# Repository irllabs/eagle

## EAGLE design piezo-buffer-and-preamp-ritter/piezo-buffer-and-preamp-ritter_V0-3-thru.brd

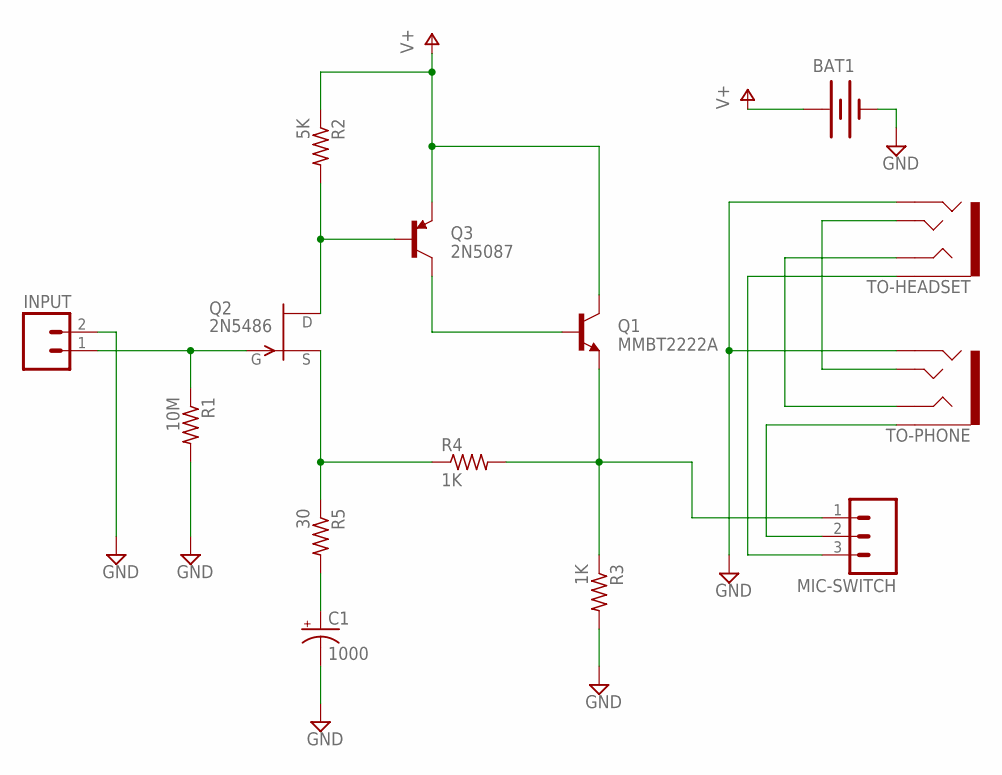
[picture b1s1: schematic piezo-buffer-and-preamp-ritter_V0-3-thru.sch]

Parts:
BAT1: BATTERYAAA-KIT; BATTERY-AAA-KIT
C1: 1000; CPOL-RADIAL-1000UF-25V
INPUT: M02LOCK; 1X02_LOCK
MIC-SWITCH: M03LOCK; 1X03_LOCK
Q1: MMBT2222A; TO-92
Q2: 2N5486; TO92-
Q3: 2N5087; TO-92
R1: 10M; V526-0
R2: 5K; V526-0
R3, R4: 1K; V526-0
R5: 30; V526-0
TO-HEADSET: AUDIO-JACK3; AUDIO-JACK-TRRS-SMD
TO-PHONE: AUDIO-JACK3; AUDIO-JACK-TRRS-SMD

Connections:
GND: BAT1.GND@1 (-), C1.-, INPUT.2, R1.2, R3.2, TO-HEADSET.RING2, TO-PHONE.RING2
unnamed: INPUT.1, Q2.1 (G), R1.1
unnamed: Q2.3 (D), Q3.2 (B), R2.2
unnamed: Q2.2 (S), R4.1, R5.1
unnamed: Q1.2 (B), Q3.3 (C)
unnamed: C1.+, R5.2
unnamed: MIC-SWITCH.3, TO-HEADSET.EARTH
unnamed: TO-HEADSET.TIP, TO-PHONE.TIP
unnamed: TO-HEADSET.RING1, TO-PHONE.RING1
TO-PHONE: MIC-SWITCH.2, TO-PHONE.EARTH
V+: BAT1.PWR@1 (+), Q1.3 (C), Q3.1 (E), R2.1
`DEL: MIC-SWITCH.1, Q1.1 (E), R3.1, R4.2

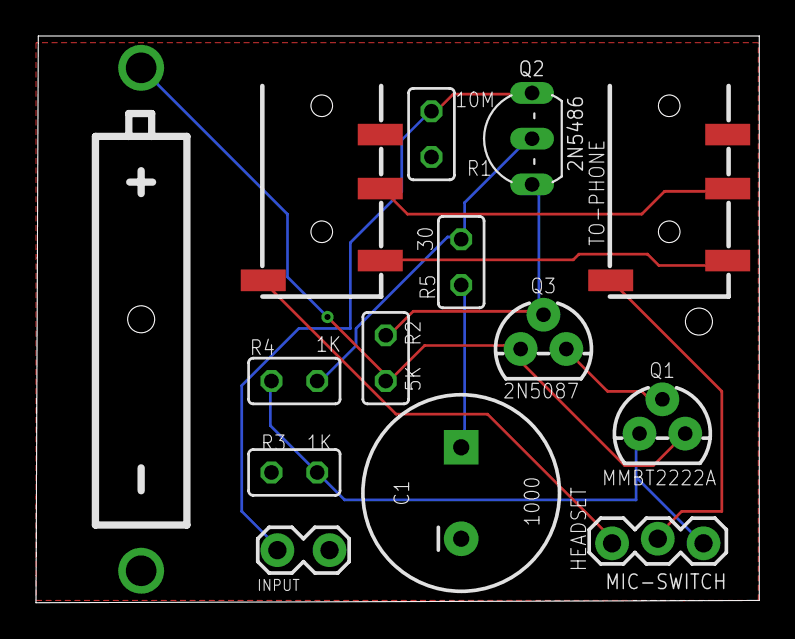
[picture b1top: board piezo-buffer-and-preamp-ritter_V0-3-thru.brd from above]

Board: 2 copper layers, 40.2 x 31.5 mm, 14 parts (0 on the bottom side), 12 nets.

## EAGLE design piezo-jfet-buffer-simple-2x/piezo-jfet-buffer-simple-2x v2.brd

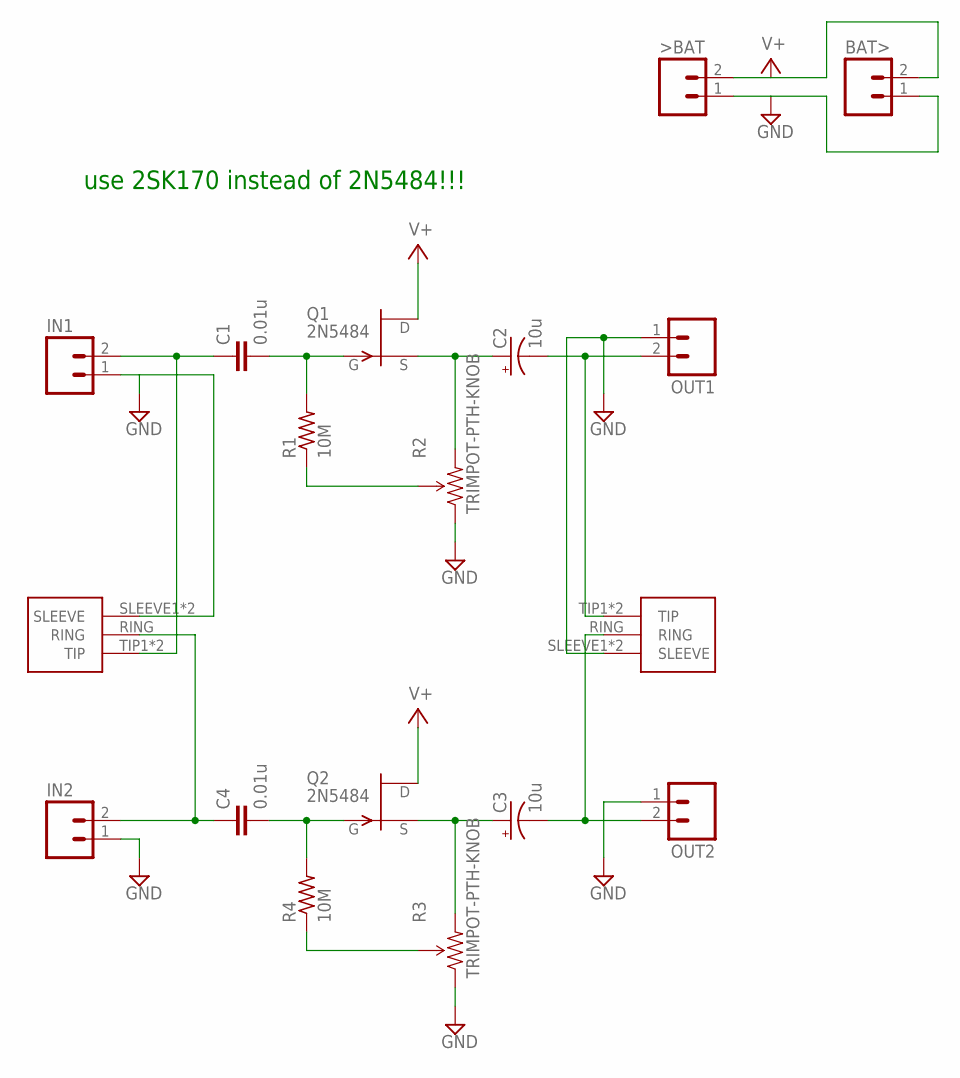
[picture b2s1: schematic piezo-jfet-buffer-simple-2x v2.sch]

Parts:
>BAT: M02PTH; 1X02
BAT>: M02PTH; 1X02
C1, C4: 0.01u; C5B3
C2, C3: 10u; CPOL-RADIAL-10UF-25V
IN1, IN2: M02LOCK; 1X02_LOCK
OUT1, OUT2: M02LOCK; 1X02_LOCK
Q1, Q2: 2N5484; TO92-
R1, R4: 10M; 0204V
R2, R3: TRIMPOT-PTH-KNOB; 3386U
U$1, U$2: 1/8"-F-STEREO-PCB

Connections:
CH1: C2.2 (-), OUT1.2, U$1.TIP1 (TIP), U$1.TIP2 (TIP)
CH2: C3.2 (-), OUT2.2, U$1.RING
GND: >BAT.1, BAT>.1, IN1.1, IN2.1, OUT1.1, OUT2.1, R2.1 (CCW), R3.1 (CCW), U$1.SLEEVE1 (SLEEVE), U$1.SLEEVE2 (SLEEVE), U$2.SLEEVE1 (SLEEVE), U$2.SLEEVE2 (SLEEVE)
JFET-GATE: C1.2, Q1.1 (G), R1.2
JFET-GATE1: C4.2, Q2.1 (G), R4.2
JFET-SOURCE: C2.1 (+), Q1.2 (S), R2.3 (CW)
JFET-SOURCE1: C3.1 (+), Q2.2 (S), R3.3 (CW)
unnamed: R3.2 (WIPER), R4.1
unnamed: C1.1, IN1.2, U$2.TIP1 (TIP), U$2.TIP2 (TIP)
unnamed: R1.1, R2.2 (WIPER)
unnamed: C4.1, IN2.2, U$2.RING
V+: >BAT.2, BAT>.2, Q1.3 (D), Q2.3 (D)

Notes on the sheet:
use 2SK170 instead of 2N5484!!!

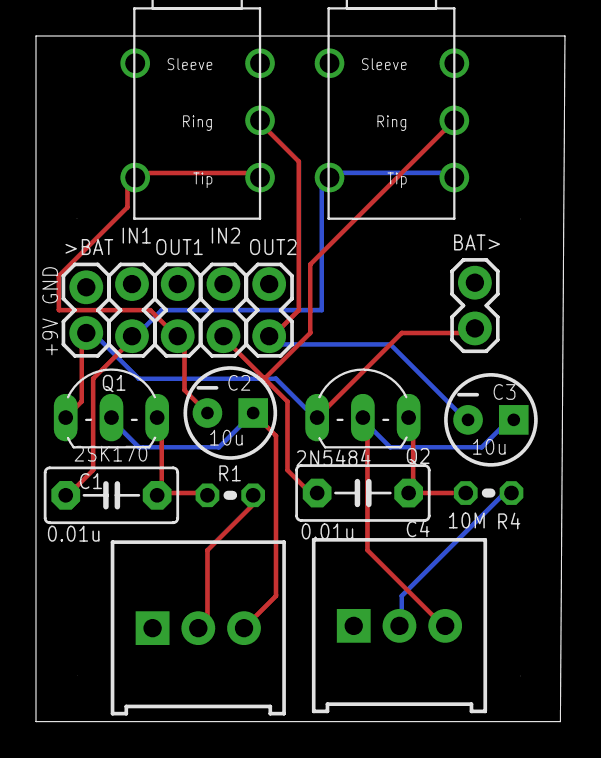
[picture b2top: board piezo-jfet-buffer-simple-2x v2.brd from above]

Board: 2 copper layers, 29.4 x 38.1 mm, 18 parts (0 on the bottom side), 12 nets.

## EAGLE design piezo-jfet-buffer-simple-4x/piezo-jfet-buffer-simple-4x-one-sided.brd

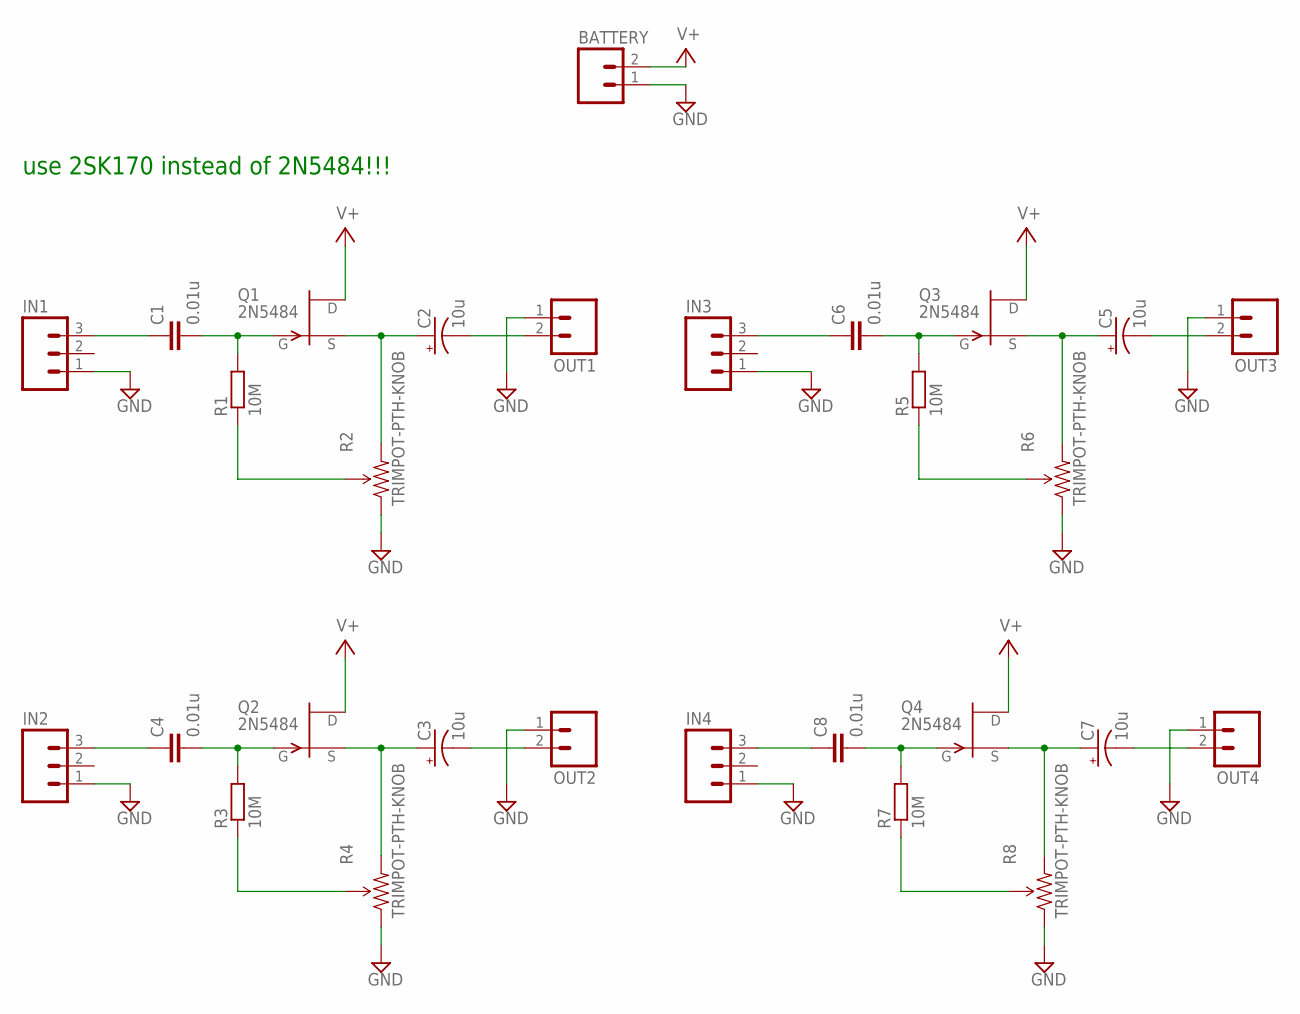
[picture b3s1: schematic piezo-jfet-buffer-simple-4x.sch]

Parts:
BATTERY: M02PTH; 1X02
C1, C4, C6, C8: 0.01u; C5B3
C2, C3, C5, C7: 10u; CPOL-RADIAL-10UF-25V
IN1, IN2, IN3, IN4: M03LOCK; 1X03_LOCK
OUT1, OUT2, OUT3, OUT4: M02LOCK; 1X02_LOCK
Q1, Q2, Q3, Q4: 2N5484; TO92-
R1, R3, R5, R7: 10M; 0204/7
R2, R4, R6, R8: TRIMPOT-PTH-KNOB; 3386U

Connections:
CH1: C2.2 (-), OUT1.2
CH2: C3.2 (-), OUT2.2
CH3: C5.2 (-), OUT3.2
CH4: C7.2 (-), OUT4.2
GND: BATTERY.1, IN1.1, IN2.1, IN3.1, IN4.1, OUT1.1, OUT2.1, OUT3.1, OUT4.1, R2.1 (CCW), R4.1 (CCW), R6.1 (CCW), R8.1 (CCW)
JFET-GATE: C1.2, Q1.1 (G), R1.2
JFET-GATE1: C4.2, Q2.1 (G), R3.2
JFET-GATE2: C6.2, Q3.1 (G), R5.2
JFET-GATE3: C8.2, Q4.1 (G), R7.2
JFET-SOURCE: C2.1 (+), Q1.2 (S), R2.3 (CW)
JFET-SOURCE1: C3.1 (+), Q2.2 (S), R4.3 (CW)
JFET-SOURCE2: C5.1 (+), Q3.2 (S), R6.3 (CW)
JFET-SOURCE3: C7.1 (+), Q4.2 (S), R8.3 (CW)
unnamed: C1.1, IN1.3
unnamed: C4.1, IN2.3
unnamed: R1.1, R2.2 (WIPER)
unnamed: R3.1, R4.2 (WIPER)
unnamed: C6.1, IN3.3
unnamed: R5.1, R6.2 (WIPER)
unnamed: C8.1, IN4.3
unnamed: R7.1, R8.2 (WIPER)
V+: BATTERY.2, Q1.3 (D), Q2.3 (D), Q3.3 (D), Q4.3 (D)

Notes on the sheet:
use 2SK170 instead of 2N5484!!!

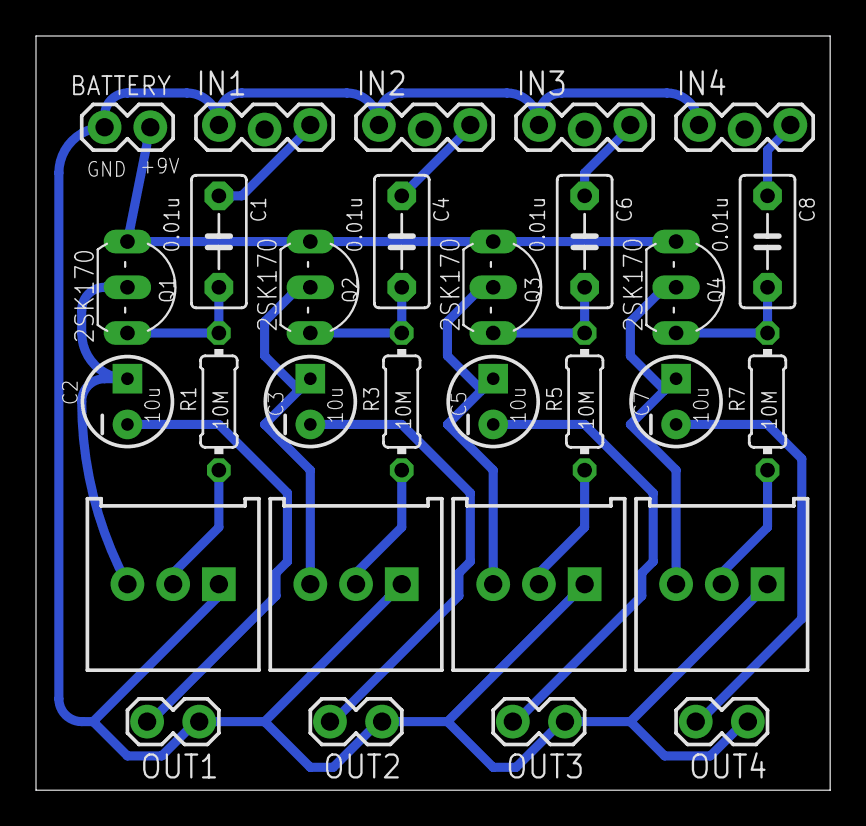
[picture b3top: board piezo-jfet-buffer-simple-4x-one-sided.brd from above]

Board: 2 copper layers, 44.1 x 41.9 mm, 29 parts (0 on the bottom side), 22 nets.

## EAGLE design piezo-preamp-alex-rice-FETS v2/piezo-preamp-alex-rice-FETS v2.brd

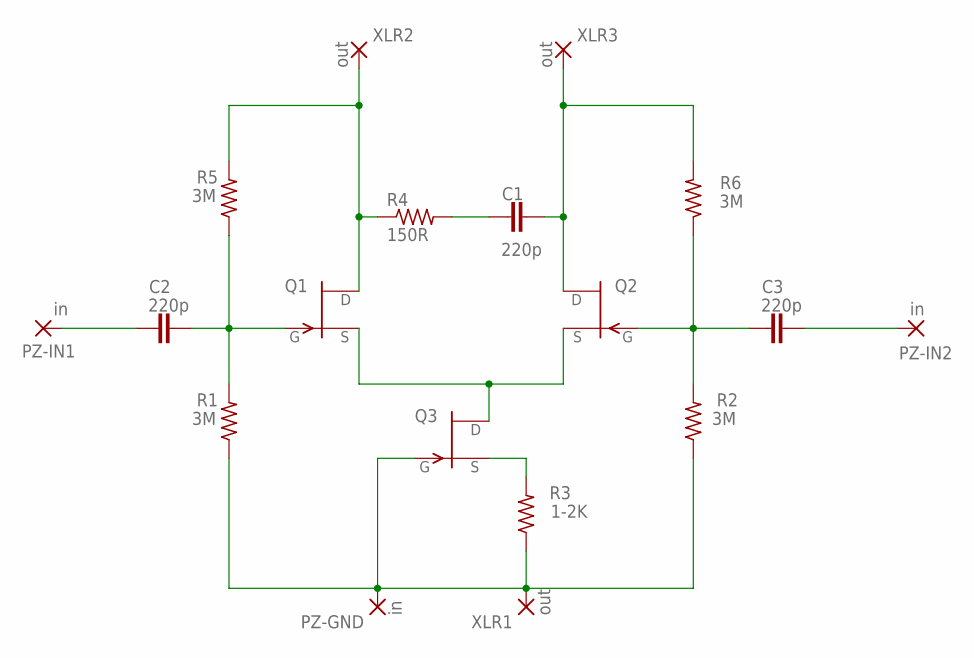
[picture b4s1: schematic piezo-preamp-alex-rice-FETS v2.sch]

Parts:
C1, C2, C3: 220p; C050-030X075
PZ-GND: in; 3,81/1,1
PZ-IN1, PZ-IN2: in; 3,81/1,1
Q1: 2N3819; TO92
Q2, Q3: 2N3819-WIDETO92_WIDE; TO92
R1, R2, R5, R6: 3M; 0414V
R3: 1-2K; 0414V
R4: 150R; 0414V
XLR1, XLR2, XLR3: out; 3,81/1,1

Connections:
GND: PZ-GND.1, Q3.2 (G), R1.1, R2.1, R3.1, XLR1.1
unnamed: Q1.1 (D), R4.1, R5.2, XLR2.1
unnamed: C1.2, Q2.1 (D), R6.2, XLR3.1
unnamed: C1.1, R4.2
unnamed: C3.1, Q2.2 (G), R2.2, R6.1
unnamed: C2.2, Q1.2 (G), R1.2, R5.1
unnamed: Q3.3 (S), R3.2
unnamed: C2.1, PZ-IN1.1
unnamed: Q1.3 (S), Q2.3 (S), Q3.1 (D)
unnamed: C3.2, PZ-IN2.1

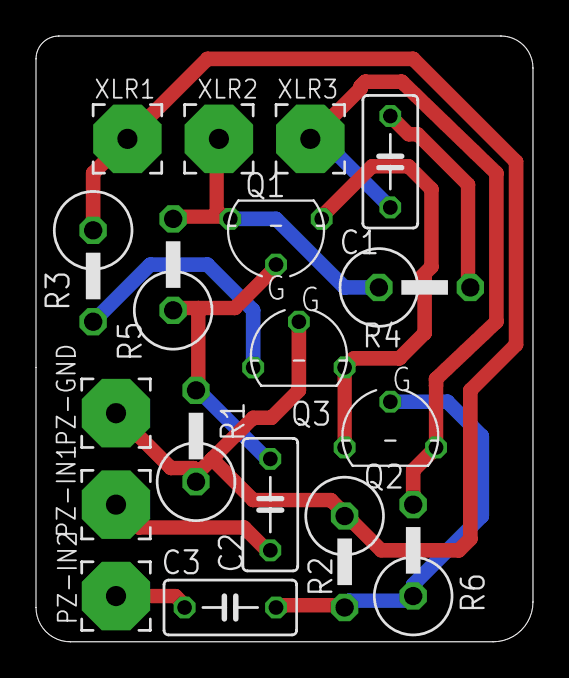
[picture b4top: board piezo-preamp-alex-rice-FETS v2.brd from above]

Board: 2 copper layers, 27.6 x 33.7 mm, 18 parts (0 on the bottom side), 10 nets.

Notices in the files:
parts and their libraries:
SparkFun-Connectors: Licensing: Creative Commons ShareAlike 4.0 International - https://creativecommons.org/licenses/by-sa/4.0
SparkFun-Connectors: Licensing: CC v3.0 Share-Alike You are welcome to use this library for commercial purposes.
